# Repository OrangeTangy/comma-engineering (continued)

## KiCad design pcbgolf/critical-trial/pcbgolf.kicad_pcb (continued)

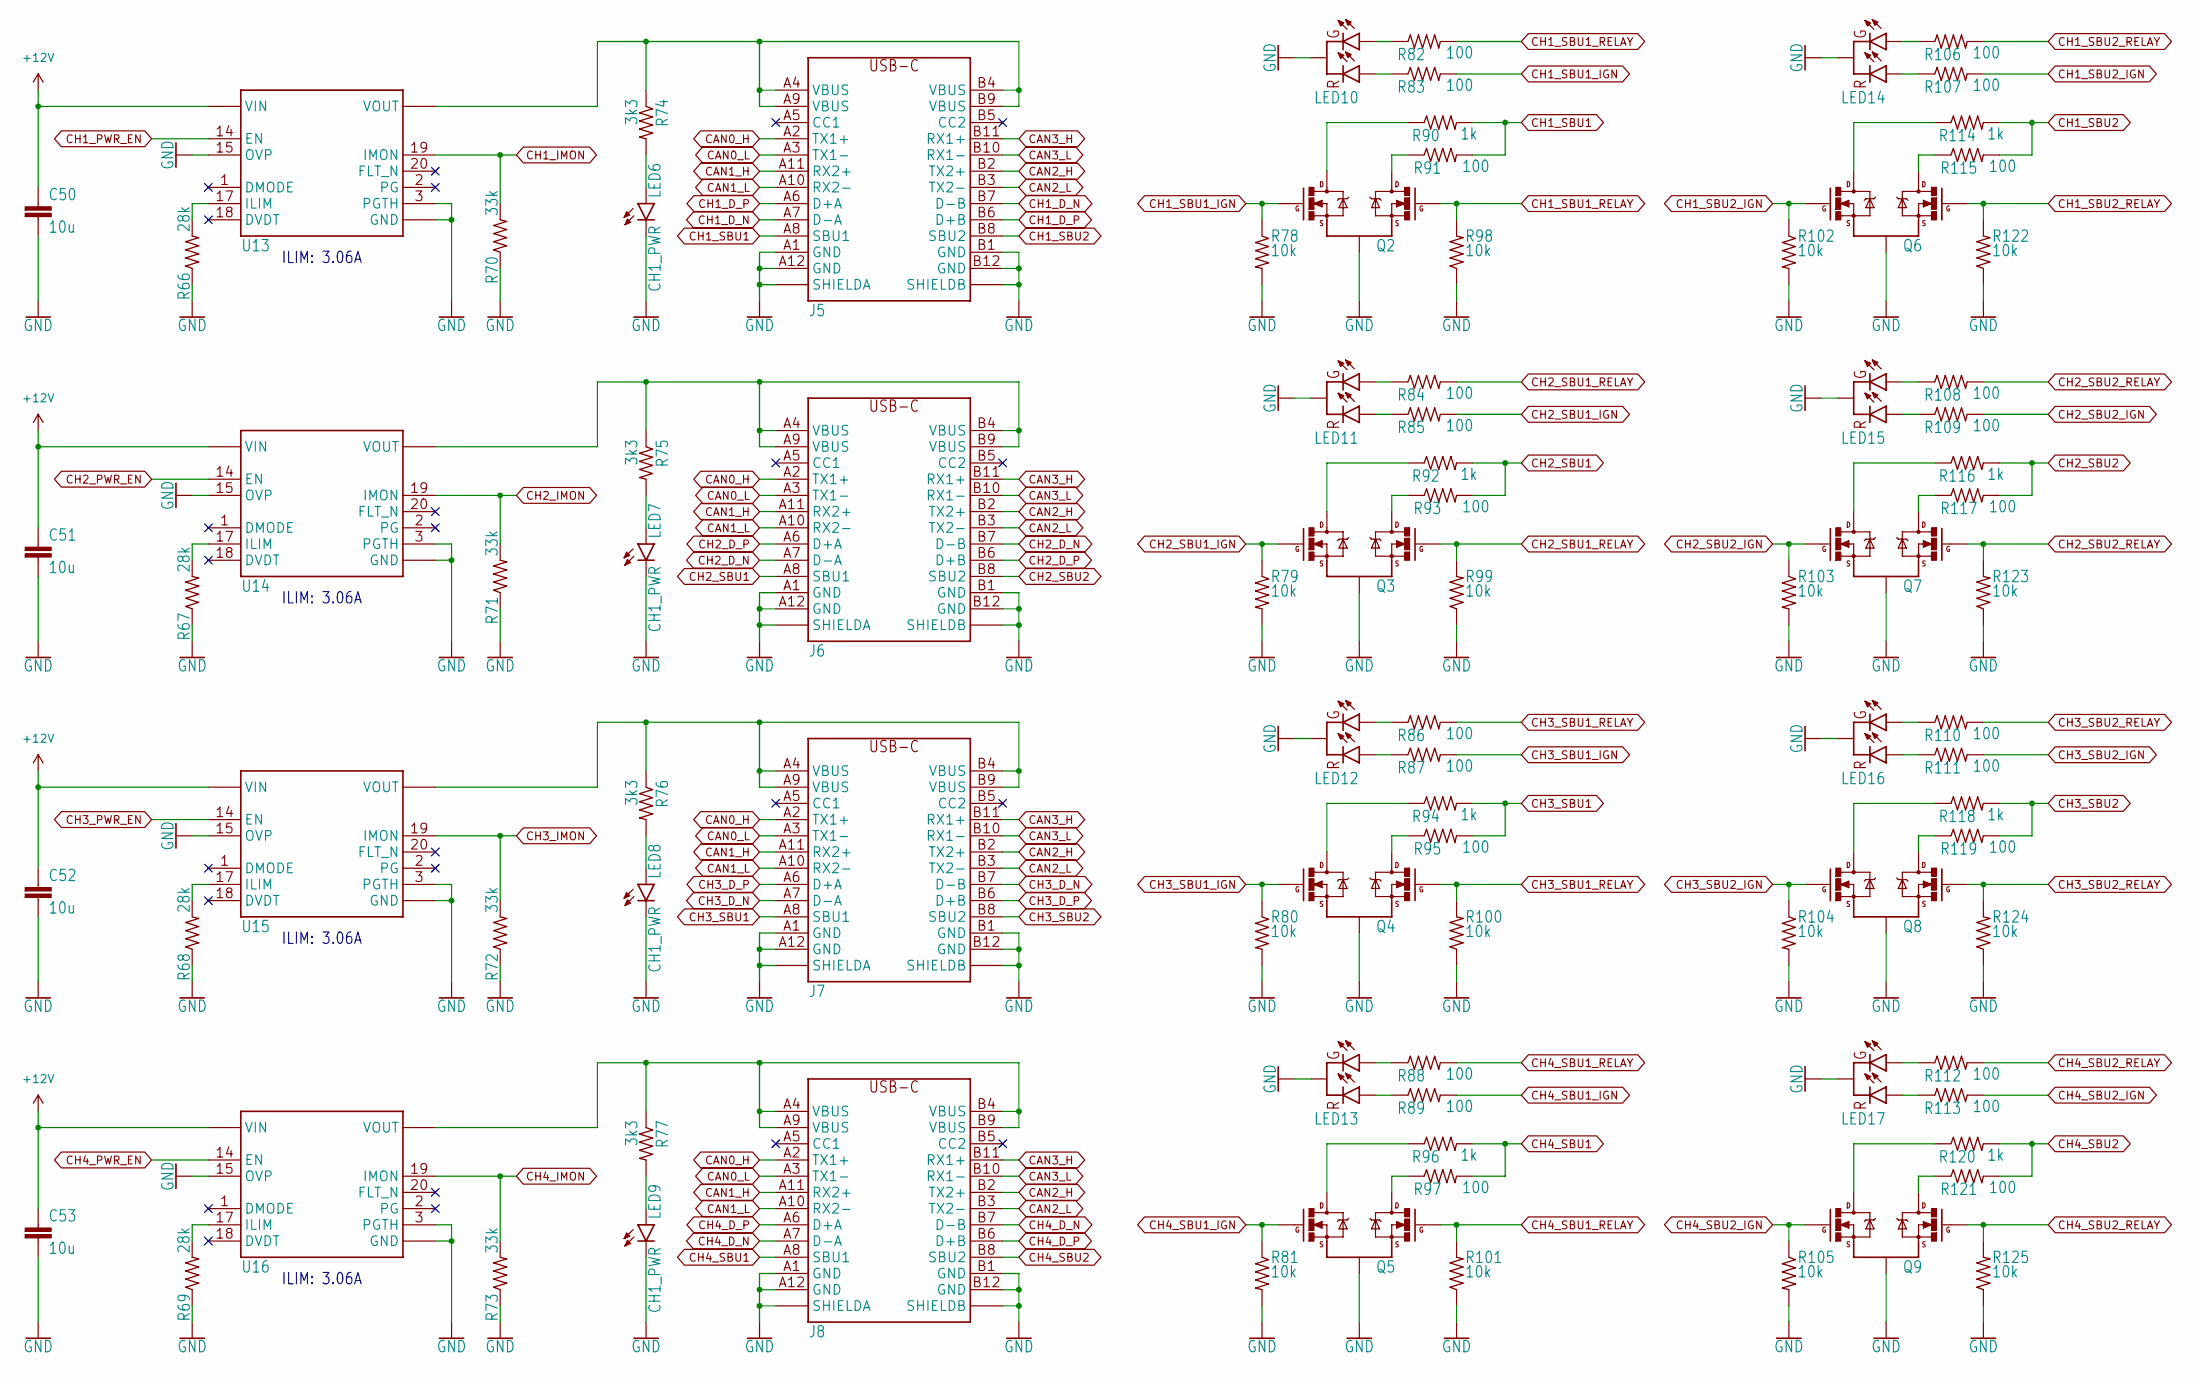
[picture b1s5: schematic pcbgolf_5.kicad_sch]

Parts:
C50, C51, C52, C53: 10u; 0805-C; MPN CL21A106KAYNNNE
J5, J6, J7, J8: USB-C-FEMALEGCT; USB-C-FEMALE-VERT-GCT; MPN 10132328-10011LF
LED6, LED7, LED8, LED9: CH1_PWR; CHIPLED; MPN LG R971-KN-1
LED10, LED11, LED12, LED13, LED14, LED15, LED16, LED17: LED-CC-GREEN-RED-AM23ESG; SOT23-3; MPN AM23ESGW
Q2, Q3, Q4, Q5, Q6, Q7, Q8, Q9: NFET-DUAL-COMMON-SOURCE-QS5K2; SOT23-5; MPN QS5K2TR
R66, R67, R68, R69: 28k; 0402-R; MPN RK73H1ETTP2802F
R70, R71, R72, R73: 33k; 0402-R; MPN RC0402JR-0733KL
R74, R75, R76, R77: 3k3; 0402-R; MPN RC0402JR-073K3L
R78, R79, R80, R81, R98, R99, R100, R101, R102, R103, R104, R105, R122, R123, R124, R125: 10k; 0402-R; MPN RC0402FR-0710KL
R82, R83, R84, R85, R86, R87, R88, R89, R91, R93, R95, R97, R106, R107, R108, R109, R110, R111, R112, R113, R115, R117, R119, R121: 100; 0402-R; MPN RC0402JR-07100RL
R90, R92, R94, R96, R114, R116, R118, R120: 1k; 0402-R; MPN RC0402JR-071KL
U13, U14, U15, U16: TPS25942; WQFN20; MPN TPS25944ARVCR

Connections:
+12V: C50.1, C51.1, C52.1, C53.1, U13.9 (VIN), U13.10 (VIN), U13.11 (VIN), U13.12 (VIN), U13.13 (VIN), U14.9 (VIN), U14.10 (VIN), U14.11 (VIN), U14.12 (VIN), U14.13 (VIN), U15.9 (VIN), U15.10 (VIN), U15.11 (VIN), U15.12 (VIN), U15.13 (VIN), U16.9 (VIN), U16.10 (VIN), U16.11 (VIN), U16.12 (VIN), U16.13 (VIN); also elsewhere on the board
CAN0_H: J5.A2 (TX1+), J6.A2 (TX1+), J7.A2 (TX1+), J8.A2 (TX1+); also elsewhere on the board
CAN0_L: J5.A3 (TX1-), J6.A3 (TX1-), J7.A3 (TX1-), J8.A3 (TX1-); also elsewhere on the board
CAN1_H: J5.A11 (RX2+), J6.A11 (RX2+), J7.A11 (RX2+), J8.A11 (RX2+); also elsewhere on the board
CAN1_L: J5.A10 (RX2-), J6.A10 (RX2-), J7.A10 (RX2-), J8.A10 (RX2-); also elsewhere on the board
CAN2_H: J5.B2 (TX2+), J6.B2 (TX2+), J7.B2 (TX2+), J8.B2 (TX2+); also elsewhere on the board
CAN2_L: J5.B3 (TX2-), J6.B3 (TX2-), J7.B3 (TX2-), J8.B3 (TX2-); also elsewhere on the board
CAN3_H: J5.B11 (RX1+), J6.B11 (RX1+), J7.B11 (RX1+), J8.B11 (RX1+); also elsewhere on the board
CAN3_L: J5.B10 (RX1-), J6.B10 (RX1-), J7.B10 (RX1-), J8.B10 (RX1-); also elsewhere on the board
CH1_D_N: J5.A7 (D-A), J5.B7 (D-B); also elsewhere on the board
CH1_D_P: J5.A6 (D+A), J5.B6 (D+B); also elsewhere on the board
CH1_IMON: R70.2, U13.19 (IMON); also elsewhere on the board
CH1_PWR_EN: U13.14 (EN); also elsewhere on the board
CH1_SBU1: J5.A8 (SBU1), R90.2, R91.2; also elsewhere on the board
CH1_SBU1_IGN: Q2.1 (G1), R78.1, R83.2; also elsewhere on the board
CH1_SBU1_RELAY: Q2.3 (G2), R82.2, R98.2; also elsewhere on the board
CH1_SBU2: J5.B8 (SBU2), R114.2, R115.2; also elsewhere on the board
CH1_SBU2_IGN: Q6.1 (G1), R102.1, R107.2; also elsewhere on the board
CH1_SBU2_RELAY: Q6.3 (G2), R106.2, R122.2; also elsewhere on the board
CH2_D_N: J6.A7 (D-A), J6.B7 (D-B); also elsewhere on the board
CH2_D_P: J6.A6 (D+A), J6.B6 (D+B); also elsewhere on the board
CH2_IMON: R71.2, U14.19 (IMON); also elsewhere on the board
CH2_PWR_EN: U14.14 (EN); also elsewhere on the board
CH2_SBU1: J6.A8 (SBU1), R92.2, R93.2; also elsewhere on the board
CH2_SBU1_IGN: Q3.1 (G1), R79.1, R85.2; also elsewhere on the board
CH2_SBU1_RELAY: Q3.3 (G2), R84.2, R99.2; also elsewhere on the board
CH2_SBU2: J6.B8 (SBU2), R116.2, R117.2; also elsewhere on the board
CH2_SBU2_IGN: Q7.1 (G1), R103.1, R109.2; also elsewhere on the board
CH2_SBU2_RELAY: Q7.3 (G2), R108.2, R123.2; also elsewhere on the board
CH3_D_N: J7.A7 (D-A), J7.B7 (D-B); also elsewhere on the board
CH3_D_P: J7.A6 (D+A), J7.B6 (D+B); also elsewhere on the board
CH3_IMON: R72.2, U15.19 (IMON); also elsewhere on the board
CH3_PWR_EN: U15.14 (EN); also elsewhere on the board
CH3_SBU1: J7.A8 (SBU1), R94.2, R95.2; also elsewhere on the board
CH3_SBU1_IGN: Q4.1 (G1), R80.1, R87.2; also elsewhere on the board
CH3_SBU1_RELAY: Q4.3 (G2), R86.2, R100.2; also elsewhere on the board
CH3_SBU2: J7.B8 (SBU2), R118.2, R119.2; also elsewhere on the board
CH3_SBU2_IGN: Q8.1 (G1), R104.1, R111.2; also elsewhere on the board
CH3_SBU2_RELAY: Q8.3 (G2), R110.2, R124.2; also elsewhere on the board
CH4_D_N: J8.A7 (D-A), J8.B7 (D-B); also elsewhere on the board
CH4_D_P: J8.A6 (D+A), J8.B6 (D+B); also elsewhere on the board
CH4_IMON: R73.2, U16.19 (IMON); also elsewhere on the board
CH4_PWR_EN: U16.14 (EN); also elsewhere on the board
CH4_SBU1: J8.A8 (SBU1), R96.2, R97.2; also elsewhere on the board
CH4_SBU1_IGN: Q5.1 (G1), R81.1, R89.2; also elsewhere on the board
CH4_SBU1_RELAY: Q5.3 (G2), R88.2, R101.2; also elsewhere on the board
CH4_SBU2: J8.B8 (SBU2), R120.2, R121.2; also elsewhere on the board
CH4_SBU2_IGN: Q9.1 (G1), R105.1, R113.2; also elsewhere on the board
CH4_SBU2_RELAY: Q9.3 (G2), R112.2, R125.2; also elsewhere on the board
GND: C50.2, C51.2, C52.2, C53.2, J5.A1 (GND), J5.A12 (GND), J5.B1 (GND), J5.B12 (GND), J5.S1 (SHIELDA), J5.S2 (SHIELDA), J5.S3 (SHIELDA), J5.S4 (SHIELDA), J5.S11 (SHIELDB), J5.S12 (SHIELDB), J5.S13 (SHIELDB), J5.S14 (SHIELDB), J6.A1 (GND), J6.A12 (GND), J6.B1 (GND), J6.B12 (GND), J6.S1 (SHIELDA), J6.S2 (SHIELDA), J6.S3 (SHIELDA), J6.S4 (SHIELDA), J6.S11 (SHIELDB), J6.S12 (SHIELDB), J6.S13 (SHIELDB), J6.S14 (SHIELDB), J7.A1 (GND), J7.A12 (GND), J7.B1 (GND), J7.B12 (GND), J7.S1 (SHIELDA), J7.S2 (SHIELDA), J7.S3 (SHIELDA), J7.S4 (SHIELDA), J7.S11 (SHIELDB), J7.S12 (SHIELDB), J7.S13 (SHIELDB), J7.S14 (SHIELDB), J8.A1 (GND), J8.A12 (GND), J8.B1 (GND), J8.B12 (GND), J8.S1 (SHIELDA), J8.S2 (SHIELDA), J8.S3 (SHIELDA), J8.S4 (SHIELDA), J8.S11 (SHIELDB), J8.S12 (SHIELDB), J8.S13 (SHIELDB), J8.S14 (SHIELDB), LED6.C, LED7.C, LED8.C, LED9.C, LED10.3 (C), LED11.3 (C), LED12.3 (C), LED13.3 (C), LED14.3 (C), LED15.3 (C), LED16.3 (C), LED17.3 (C), Q2.2 (S), Q3.2 (S), Q4.2 (S), Q5.2 (S), Q6.2 (S), Q7.2 (S), Q8.2 (S), Q9.2 (S), R66.1, R67.1, R68.1, R69.1, R70.1, R71.1, R72.1, R73.1, R78.2, R79.2, R80.2, R81.2, R98.1, R99.1, R100.1, R101.1, R102.2, R103.2, R104.2, R105.2, R122.1, R123.1, R124.1, R125.1, U13.3 (PGTH), U13.15 (OVP), U13.16 (GND), U13.PAD (GND), U14.3 (PGTH), U14.15 (OVP), U14.16 (GND), U14.PAD (GND), U15.3 (PGTH), U15.15 (OVP), U15.16 (GND), U15.PAD (GND), U16.3 (PGTH), U16.15 (OVP), U16.16 (GND), U16.PAD (GND); also elsewhere on the board
unnamed: J5.A4 (VBUS), J5.A9 (VBUS), J5.B4 (VBUS), J5.B9 (VBUS), R74.1, U13.4 (VOUT), U13.5 (VOUT), U13.6 (VOUT), U13.7 (VOUT), U13.8 (VOUT)
unnamed: J6.A4 (VBUS), J6.A9 (VBUS), J6.B4 (VBUS), J6.B9 (VBUS), R75.1, U14.4 (VOUT), U14.5 (VOUT), U14.6 (VOUT), U14.7 (VOUT), U14.8 (VOUT)
unnamed: J7.A4 (VBUS), J7.A9 (VBUS), J7.B4 (VBUS), J7.B9 (VBUS), R76.1, U15.4 (VOUT), U15.5 (VOUT), U15.6 (VOUT), U15.7 (VOUT), U15.8 (VOUT)
unnamed: J8.A4 (VBUS), J8.A9 (VBUS), J8.B4 (VBUS), J8.B9 (VBUS), R77.1, U16.4 (VOUT), U16.5 (VOUT), U16.6 (VOUT), U16.7 (VOUT), U16.8 (VOUT)
unnamed: LED6.A, R74.2
unnamed: LED7.A, R75.2
unnamed: LED8.A, R76.2
unnamed: LED9.A, R77.2
unnamed: LED10.2 (AG), R82.1
unnamed: LED10.1 (AR), R83.1
unnamed: LED11.2 (AG), R84.1
unnamed: LED11.1 (AR), R85.1
unnamed: LED12.2 (AG), R86.1
unnamed: LED12.1 (AR), R87.1
unnamed: LED13.2 (AG), R88.1
unnamed: LED13.1 (AR), R89.1
unnamed: LED14.2 (AG), R106.1
unnamed: LED14.1 (AR), R107.1
unnamed: LED15.2 (AG), R108.1
unnamed: LED15.1 (AR), R109.1
unnamed: LED16.2 (AG), R110.1
unnamed: LED16.1 (AR), R111.1
unnamed: LED17.2 (AG), R112.1
unnamed: LED17.1 (AR), R113.1
unnamed: Q2.5 (D1), R90.1
unnamed: Q2.4 (D2), R91.1
unnamed: Q3.5 (D1), R92.1
unnamed: Q3.4 (D2), R93.1
unnamed: Q4.5 (D1), R94.1
unnamed: Q4.4 (D2), R95.1
unnamed: Q5.5 (D1), R96.1
unnamed: Q5.4 (D2), R97.1
unnamed: Q6.5 (D1), R114.1
unnamed: Q6.4 (D2), R115.1
unnamed: Q7.5 (D1), R116.1
unnamed: Q7.4 (D2), R117.1
unnamed: Q8.5 (D1), R118.1
unnamed: Q8.4 (D2), R119.1
unnamed: Q9.5 (D1), R120.1
unnamed: Q9.4 (D2), R121.1
unnamed: R66.2, U13.17 (ILIM)
unnamed: R67.2, U14.17 (ILIM)
unnamed: R68.2, U15.17 (ILIM)
unnamed: R69.2, U16.17 (ILIM)

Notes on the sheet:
ILIM: 3.06A

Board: 2 copper layers, 245 parts (47 on the bottom side), 191 nets, no tracks yet.
